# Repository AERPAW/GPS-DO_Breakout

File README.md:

# GPS-DO_Breakout

BOM:
https://docs.google.com/spreadsheets/d/1a5mKvM8TDBHcoS5wY0aij9EXUGsqO3GlbDBUkMFTzfU/edit#gid=0

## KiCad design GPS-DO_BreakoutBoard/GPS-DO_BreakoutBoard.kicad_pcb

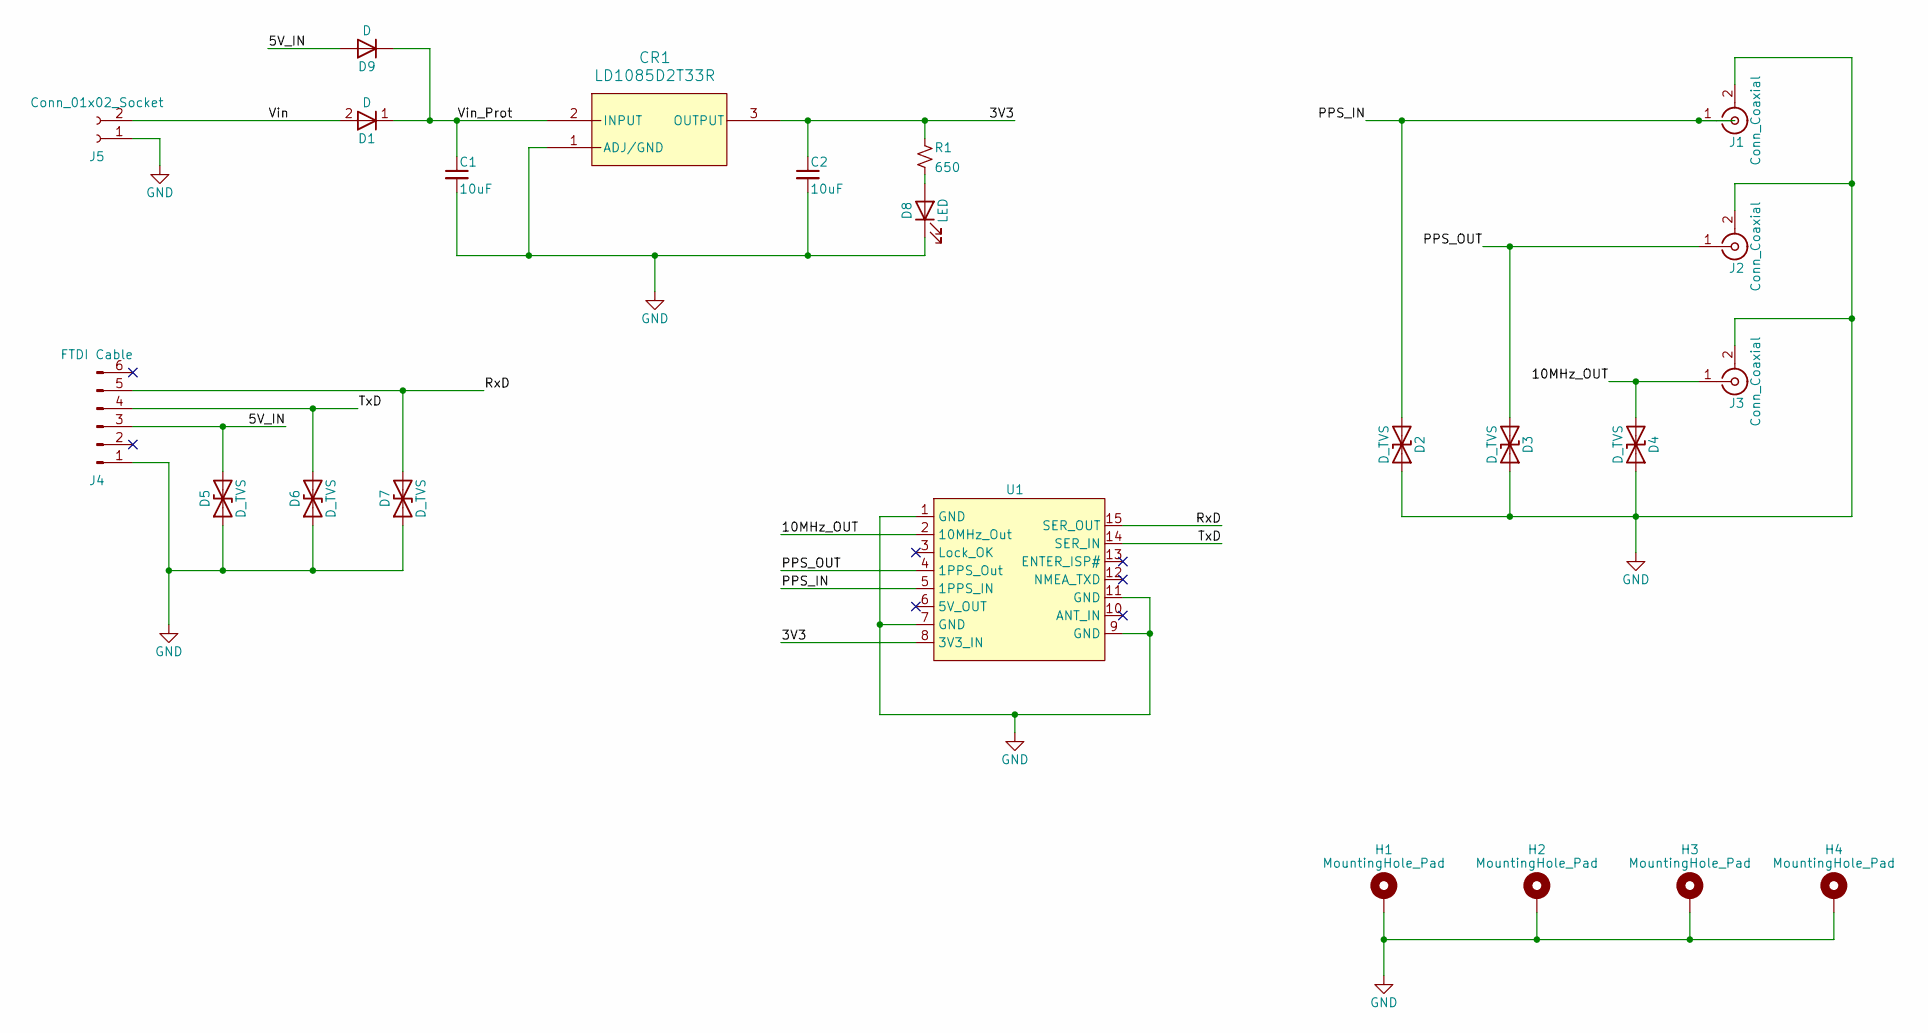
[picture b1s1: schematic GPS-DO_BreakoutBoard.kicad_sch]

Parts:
C1, C2: 10uF; C_1206_3216Metric
CR1: LD1085D2T33R; D2PAK_STM
D1, D9: D; 2x1_POWERDI-5_SBRT10U50SP5_DIO
D2, D3, D4, D5, D6, D7: D_TVS; D_SMA
D8: LED; LED_1206_3216Metric
H1, H2, H3, H4: MountingHole_Pad; MountingHole_3.2mm_M3_DIN965_Pad
J1, J2, J3: Conn_Coaxial; TAOGLAS_EMPCB.SMAFSTJ.B.HT
J4: FTDI Cable; PinHeader_1x06_P2.54mm_Horizontal
J5: Conn_01x02_Socket; CONN_1843790
R1: 650; R_1206_3216Metric
U1: 15 Pin GPSDO

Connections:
/3V3: C2.1, CR1.3 (OUTPUT), R1.1, U1.8 (3V3_IN)
/5V_IN: D5.2 (A2), D9.2 (A), J4.3
/10MHz_OUT: D4.2 (A2), J3.1 (In), U1.2 (10MHz_Out)
/PPS_IN: D2.2 (A2), J1.1 (In), U1.5 (1PPS_IN)
/PPS_OUT: D3.2 (A2), J2.1 (In), U1.4 (1PPS_Out)
/RxD: D7.2 (A2), J4.5, U1.15 (SER_OUT)
/TxD: D6.2 (A2), J4.4, U1.14 (SER_IN)
/Vin: D1.2 (A), J5.2
/Vin_Prot: C1.1, CR1.2 (INPUT), D1.1 (K), D9.1 (K)
GND: C1.2, C2.2, CR1.1 (ADJ/GND), D2.1 (A1), D3.1 (A1), D4.1 (A1), D5.1 (A1), D6.1 (A1), D7.1 (A1), D8.1 (K), H1.1, H2.1, H3.1, H4.1, J1.2 (Ext), J2.2 (Ext), J3.2 (Ext), J4.1, J5.1, U1.1 (GND), U1.7 (GND), U1.9 (GND), U1.11 (GND)
unnamed: D8.2 (A), R1.2

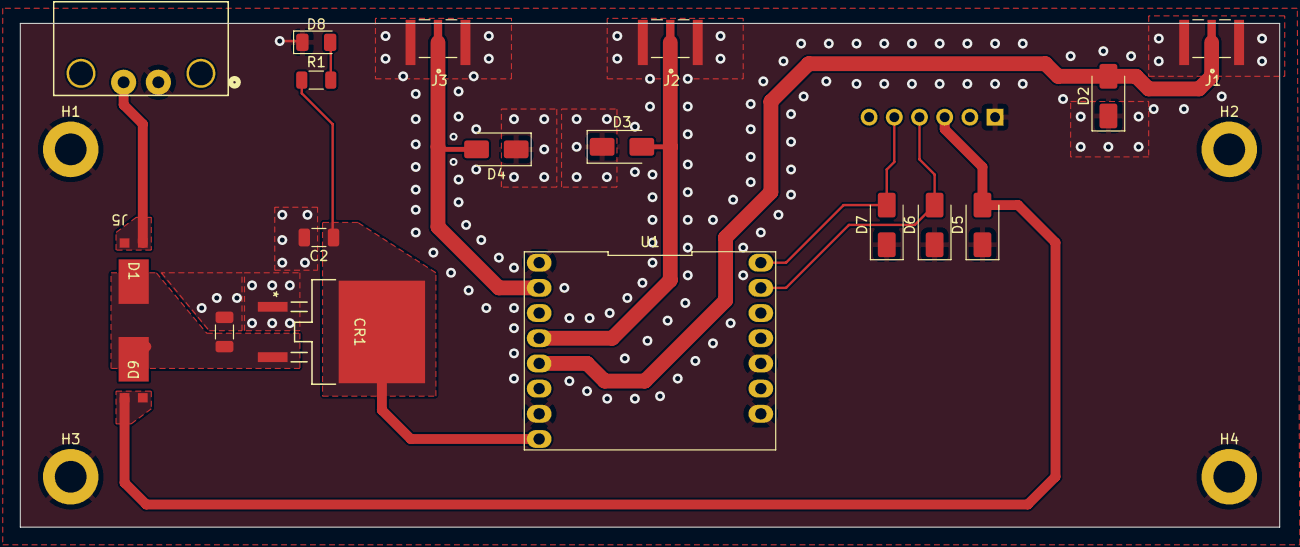
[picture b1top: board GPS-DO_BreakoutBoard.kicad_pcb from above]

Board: 2 copper layers, 127.0 x 50.8 mm, 23 parts (1 on the bottom side), 11 nets.

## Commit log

2023-06-09 inital commit
2023-06-10 Finsied 0.1 Draft of PCB
2023-06-10 added 3d view and schematic pdf
2023-06-10 added sch png
2023-06-16 V1.0 Submitted for ordering
2023-07-25 Added STEP of PCB
